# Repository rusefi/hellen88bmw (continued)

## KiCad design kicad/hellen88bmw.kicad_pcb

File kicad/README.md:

Part of https://github.com/andreika-git/hellen-one family

https://docs.google.com/spreadsheets/d/1OiEaak7TElKwF-fXWvl9Dk-fD84a0NENe6lOwhXiOe4/

Inspired by https://github.com/rusefi/hw_88_bmw

https://github.com/rusefi/hw_microRusEfi

We shall start from https://github.com/rusefi/hellen121vag but using https://github.com/rusefi/hw_88_bmw shape and pinout.

Plan:

1) merge https://github.com/rusefi/hellen121vag MCU stuff with shape of https://github.com/rusefi/hw_88_bmw

from https://github.com/rusefi/hw_88_bmw we keep
   1) outline
   2) ignition coil drivers (we actually add two more - hw_88_bmw was a 6 cylinder board, we make a 8 cylinder ECU)
   3) MAP sensor position
   4) keep SD card somewhere
   5) 88 jumpers

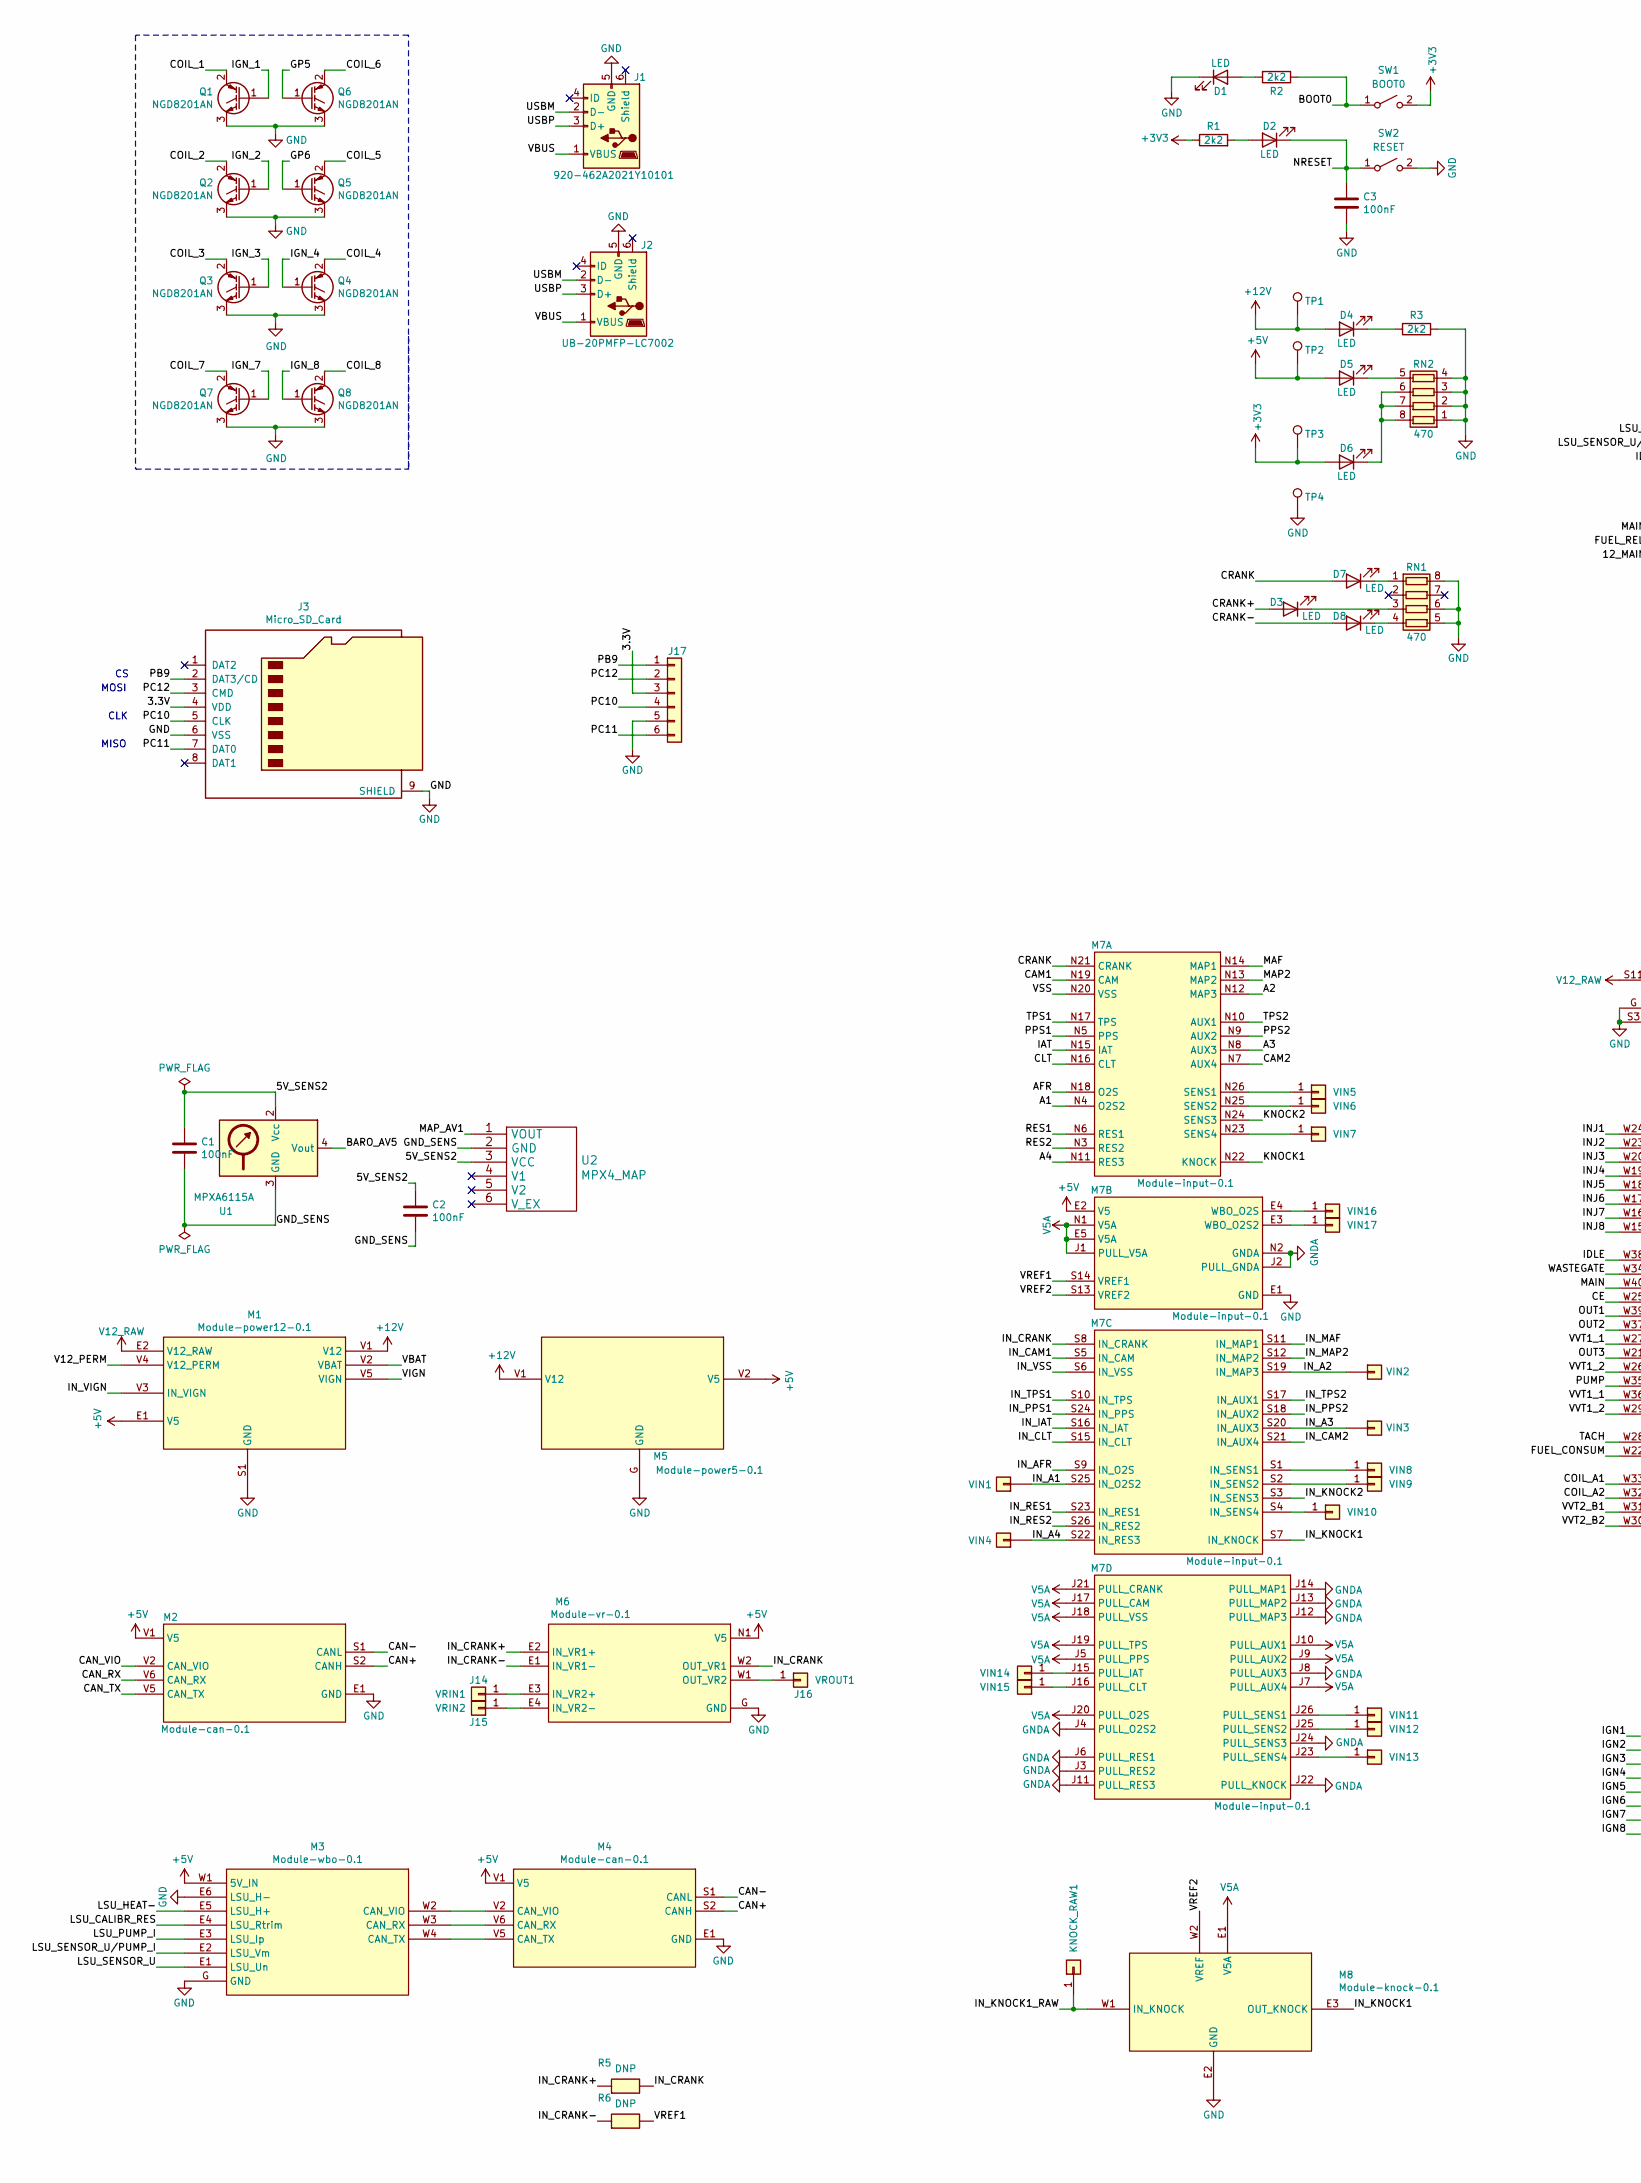
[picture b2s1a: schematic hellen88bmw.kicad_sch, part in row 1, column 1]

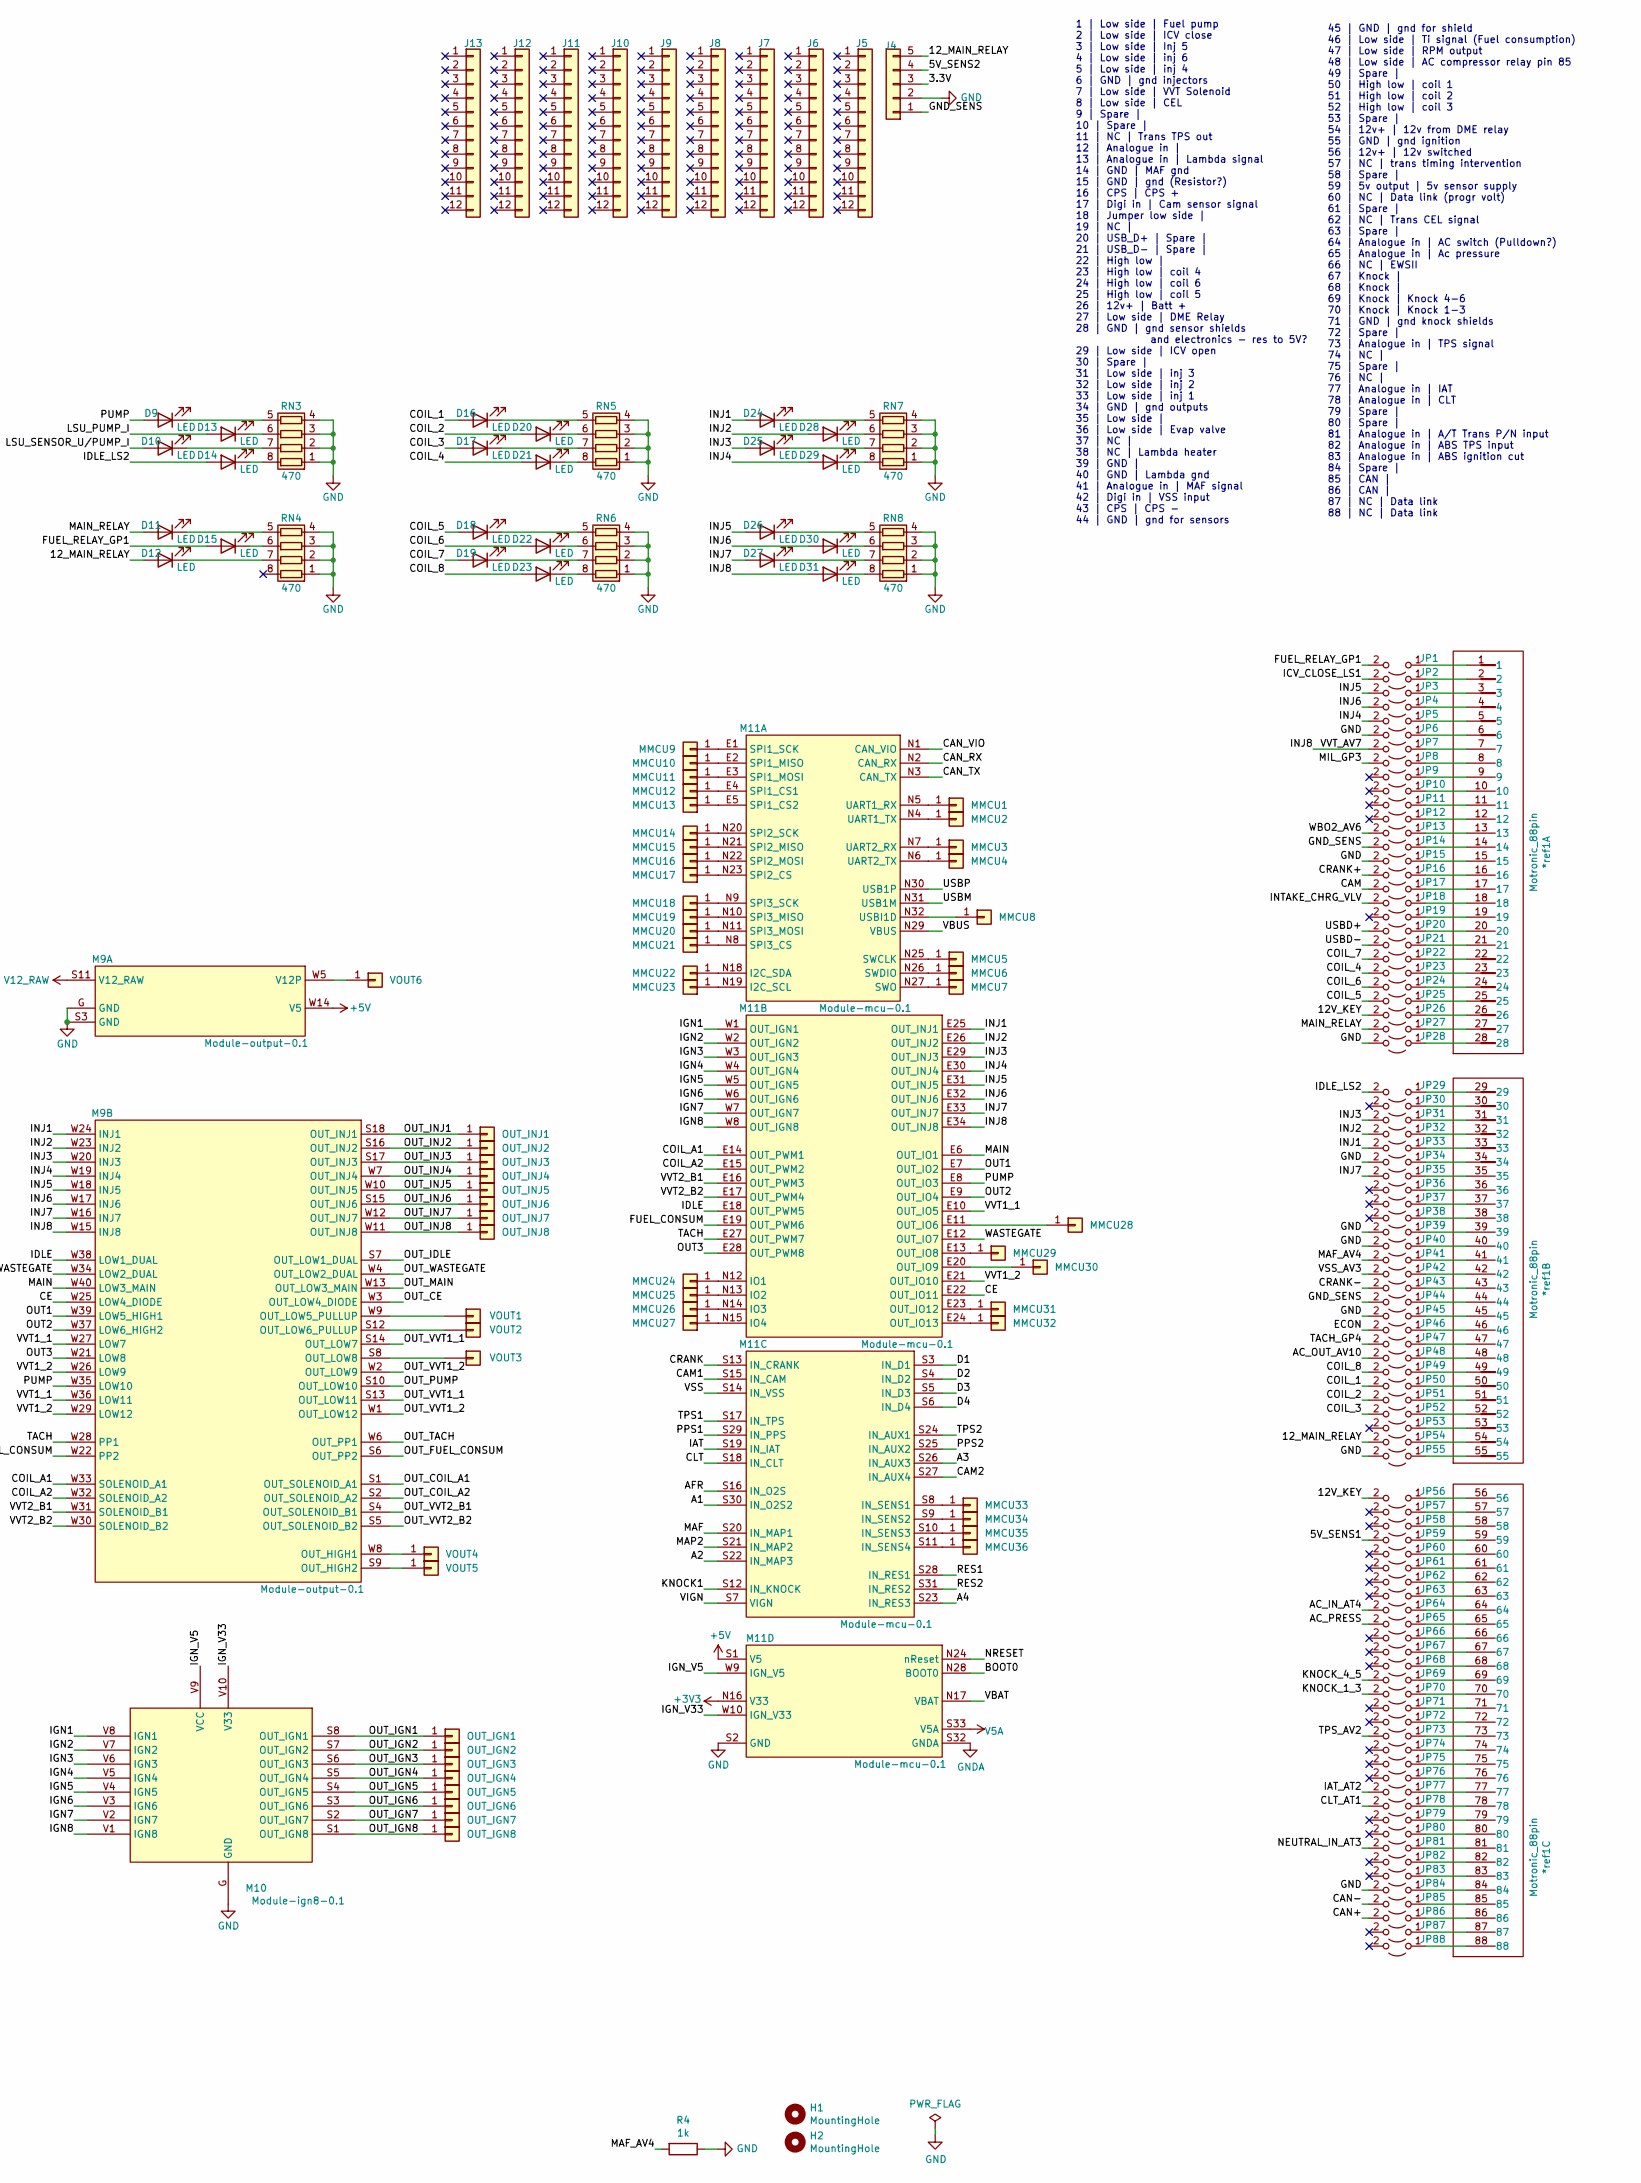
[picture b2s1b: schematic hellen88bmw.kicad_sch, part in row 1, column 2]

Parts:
*ref1: Motronic_88pin; 88pin_STS
C1, C2, C3: 100nF; C_0603_1608Metric; LCSC C49678
D1, D2, D3, D4, D5, D6, D7, D8, D9, D10, D11, D12, D13, D14, D15, D16, D17, D18, D19, D20, D21, D22, D23, D24, D25, D26, D27, D28, D29, D30, D31: LED; LED_0603_1608Metric
H1, H2: MountingHole; MountingHole_4.3mm_M4_DIN965
J1: 920-462A2021Y10101; USB-MINI-B-VERTICAL; LCSC C13453
J2: UB-20PMFP-LC7002; PinHeader_1x05_P2.00mm_Vertical; LCSC C13453
J3: Micro_SD_Card; 693072010801
J4: Conn_01x05; PinHeader_1x05_P2.54mm_Vertical
J5, J6, J7, J8, J9, J10, J11, J12, J13: Conn_01x12; PinHeader_1x12_P2.54mm_Vertical
J14: VRIN1; PinHeader_1x01_P1.00mm_Vertical
J15: VRIN2; PinHeader_1x01_P1.00mm_Vertical
J16: VROUT1; PinHeader_1x01_P1.00mm_Vertical
J17: SD; PinHeader_1x06_P2.54mm_Vertical
JP1: Jumper_2_Open; SM0805_jumper; LCSC C17477
JP2, JP3, JP4, JP5, JP6, JP7, JP8, JP9, JP10, JP11, JP12, JP13, JP14, JP15, JP16, JP17, JP18, JP19, JP20, JP21, JP22, JP23, JP24, JP25, JP26, JP27, JP28, JP29, JP30, JP31, JP32, JP33, JP34, JP35, JP36, JP37, JP38, JP39, JP40, JP41, JP42, JP43, JP44, JP45, JP46, JP47, JP48, JP49, JP50, JP51, JP52, JP53, JP54, JP55, JP56, JP57, JP58, JP59, JP60, JP61, JP62, JP63, JP64, JP65, JP66, JP67, JP68, JP69, JP70, JP71, JP72, JP73, JP74, JP75, JP76, JP77, JP78, JP79, JP80, JP81, JP82, JP83, JP84, JP85, JP86, JP87, JP88: Jumper_2_Open; SM0805_jumper
KNOCK_RAW1: IN_KNOCK1_RAW; PinHeader_1x01_P1.00mm_Vertical
M1: Module-power12-0.1; MOD_HELLEN_POWER_12
M2, M4: Module-can-0.1; MOD_HELLEN_CAN
M3: Module-wbo-0.1; MOD_HELLEN_WBO
M5: Module-power5-0.1; MOD_HELLEN_POWER_5
M6: Module-vr-0.1; MOD_HELLEN_VR
M7: Module-input-0.1; MOD_HELLEN_INPUT
M8: Module-knock-0.1; MOD_HELLEN_KNOCK
M9: Module-output-0.1; MOD_HELLEN_OUTPUT
M10: Module-ign8-0.1; MOD_HELLEN_IGN8
M11: Module-mcu-0.1; MOD_HELLEN_MCU
MMCU1: MMCU1; PinHeader_1x01_P1.00mm_Vertical
MMCU2, MMCU3, MMCU4, MMCU5, MMCU6, MMCU7, MMCU8, MMCU9, MMCU10, MMCU11, MMCU12, MMCU13, MMCU14, MMCU15, MMCU16, MMCU17, MMCU18, MMCU19, MMCU20, MMCU21, MMCU22, MMCU23, MMCU24, MMCU25, MMCU26, MMCU27, MMCU28, MMCU29, MMCU30, MMCU31, MMCU32, MMCU33, MMCU34, MMCU35, MMCU36: MMCU; PinHeader_1x01_P1.00mm_Vertical
OUT_IGN1: OUT_IGN1; PinHeader_1x01_P1.00mm_Vertical
OUT_IGN2: OUT_IGN2; PinHeader_1x01_P1.00mm_Vertical
OUT_IGN3: OUT_IGN3; PinHeader_1x01_P1.00mm_Vertical
OUT_IGN4: OUT_IGN4; PinHeader_1x01_P1.00mm_Vertical
OUT_IGN5: OUT_IGN5; PinHeader_1x01_P1.00mm_Vertical
OUT_IGN6: OUT_IGN6; PinHeader_1x01_P1.00mm_Vertical
OUT_IGN7: OUT_IGN7; PinHeader_1x01_P1.00mm_Vertical
OUT_IGN8: OUT_IGN8; PinHeader_1x01_P1.00mm_Vertical
OUT_INJ1: OUT_INJ1; PinHeader_1x01_P1.00mm_Vertical
OUT_INJ2: OUT_INJ2; PinHeader_1x01_P1.00mm_Vertical
OUT_INJ3: OUT_INJ3; PinHeader_1x01_P1.00mm_Vertical
OUT_INJ4: OUT_INJ4; PinHeader_1x01_P1.00mm_Vertical
OUT_INJ5: OUT_INJ5; PinHeader_1x01_P1.00mm_Vertical
OUT_INJ6: OUT_INJ6; PinHeader_1x01_P1.00mm_Vertical
OUT_INJ7: OUT_INJ7; PinHeader_1x01_P1.00mm_Vertical
OUT_INJ8: OUT_INJ8; PinHeader_1x01_P1.00mm_Vertical
Q1, Q2, Q3, Q4, Q5, Q7, Q8: NGD8201AN; TO-252-2
Q6: NGD8201AN; TO-252-2; LCSC C151649
R1, R2, R3: 2k2; R_0603_1608Metric
R4: 1k; R_0603_1608Metric; LCSC C17513
R5, R6: DNP; R_0603_1608Metric
RN1, RN2, RN3, RN4, RN5, RN6, RN7, RN8: 470; R_Array_Concave_4x0603
SW1: BOOT0; SW_SPST_B3U-1000P-B
SW2: RESET; SW_SPST_B3U-1000P-B
TP1, TP2, TP3, TP4: TestPoint; TestPoint_Pad_D1.0mm
U1: MPXA6115A; SSO-8_6.8x5.9mm_P1.27mm_Clearance7mm
U2: MPX4_MAP; MPX-4_MAP
VIN1, VIN2, VIN3, VIN4: Pad; PinHeader_1x01_P1.00mm_Vertical
VIN5: VIN5; PinHeader_1x01_P1.00mm_Vertical
VIN6: VIN6; PinHeader_1x01_P1.00mm_Vertical
VIN7: VIN7; PinHeader_1x01_P1.00mm_Vertical
VIN8: VIN8; PinHeader_1x01_P1.00mm_Vertical
VIN9: VIN9; PinHeader_1x01_P1.00mm_Vertical
VIN10: VIN10; PinHeader_1x01_P1.00mm_Vertical
VIN11: VIN11; PinHeader_1x01_P1.00mm_Vertical
VIN12: VIN12; PinHeader_1x01_P1.00mm_Vertical
VIN13: VIN13; PinHeader_1x01_P1.00mm_Vertical
VIN14: VIN14; PinHeader_1x01_P1.00mm_Vertical
VIN15: VIN15; PinHeader_1x01_P1.00mm_Vertical
VIN16: VIN16; PinHeader_1x01_P1.00mm_Vertical
VIN17: VIN17; PinHeader_1x01_P1.00mm_Vertical
VOUT1, VOUT2, VOUT3: Pad; PinHeader_1x01_P1.00mm_Vertical
VOUT4: VOUT4; PinHeader_1x01_P1.00mm_Vertical
VOUT5: VOUT5; PinHeader_1x01_P1.00mm_Vertical
VOUT6: VOUT6; PinHeader_1x01_P1.00mm_Vertical

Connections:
+3V3: D6.2 (A), M11.N16 (V33), R1.1, SW1.2 (B), TP3.1
+5V: D5.2 (A), M1.E1 (V5), M2.V1 (V5), M3.W1 (5V_IN), M4.V1 (V5), M5.V2 (V5), M6.N1 (V5), M7.E2 (V5), M9.W14 (V5), M11.S1 (V5), TP2.1
+12V: D4.2 (A), M1.V1 (V12), M5.V1 (V12), TP1.1
/3.3V: J3.4 (VDD), J4.3, J17.3
/5V_SENS1: JP59.2 (B)
/5V_SENS2: C1.1, C2.1, J4.4, U1.2 (Vcc), U2.3 (VCC)
/12V_KEY: JP26.2 (B), JP56.2 (B)
/12_MAIN_RELAY: D12.2 (A), J4.5, JP54.2 (B)
/A1: M7.N4 (O2S2), M11.S30 (IN_O2S2)
/A2: M7.N12 (MAP3), M11.S22 (IN_MAP3)
/A3: M7.N8 (AUX3), M11.S26 (IN_AUX3)
/A4: M7.N11 (RES3), M11.S23 (IN_RES3)
/AC_IN_AT4: JP64.2 (B)
/AC_OUT_AV10: JP48.2 (B)
/AC_PRESS: JP65.2 (B)
/AFR: M7.N18 (O2S), M11.S16 (IN_O2S)
/BARO_AV5: U1.4 (Vout)
/BOOT0: M11.N28 (BOOT0), R2.1, SW1.1 (A)
/CAM: JP17.2 (B)
/CAM1: M7.N19 (CAM), M11.S15 (IN_CAM)
/CAM2: M7.N7 (AUX4), M11.S27 (IN_AUX4)
/CAN+: JP86.2 (B), M2.S2 (CANH), M4.S2 (CANH)
/CAN-: JP85.2 (B), M2.S1 (CANL), M4.S1 (CANL)
/CAN_RX: M2.V6 (CAN_RX), M11.N2 (CAN_RX)
/CAN_TX: M2.V5 (CAN_TX), M11.N3 (CAN_TX)
/CAN_VIO: M2.V2 (CAN_VIO), M11.N1 (CAN_VIO)
/CE: M9.W25 (LOW4_DIODE), M11.E22 (OUT_IO11)
/CLT: M7.N16 (CLT), M11.S18 (IN_CLT)
/CLT_AT1: JP78.2 (B)
/COIL_1: D16.2 (A), JP50.2 (B), Q1.2 (C)
/COIL_2: D20.2 (A), JP51.2 (B), Q2.2 (C)
/COIL_3: D17.2 (A), JP52.2 (B), Q3.2 (C)
/COIL_4: D21.2 (A), JP23.2 (B), Q4.2 (C)
/COIL_5: D18.2 (A), JP25.2 (B), Q5.2 (C)
/COIL_6: D22.2 (A), JP24.2 (B), Q6.2 (C)
/COIL_7: D19.2 (A), JP22.2 (B), Q7.2 (C)
/COIL_8: D23.2 (A), JP49.2 (B), Q8.2 (C)
/COIL_A1: M9.W33 (SOLENOID_A1), M11.E14 (OUT_PWM1)
/COIL_A2: M9.W32 (SOLENOID_A2), M11.E15 (OUT_PWM2)
/CRANK: D7.2 (A), M7.N21 (CRANK), M11.S13 (IN_CRANK)
/CRANK+: D3.2 (A), JP16.2 (B)
/CRANK-: D8.2 (A), JP43.2 (B)
/D1: M11.S3 (IN_D1)
/D2: M11.S4 (IN_D2)
/D3: M11.S5 (IN_D3)
/D4: M11.S6 (IN_D4)
/ECON: JP46.2 (B)
/FUEL_CONSUM: M9.W22 (PP2), M11.E19 (OUT_PWM6)
/FUEL_RELAY_GP1: D15.2 (A), JP1.2 (B)
/GND_SENS: C1.2, C2.2, J4.1, JP14.2 (B), JP44.2 (B), U1.3 (GND), U2.2 (GND)
/GP5: Q6.1 (G)
/GP6: Q5.1 (G)
/IAT: M7.N15 (IAT), M11.S19 (IN_IAT)
/IAT_AT2: JP77.2 (B)
/ICV_CLOSE_LS1: JP2.2 (B)
/IDLE: M9.W38 (LOW1_DUAL), M11.E18 (OUT_PWM5)
/IDLE_LS2: D14.2 (A), JP29.2 (B)
/IGN1: M10.V8 (IGN1), M11.W1 (OUT_IGN1)
/IGN2: M10.V7 (IGN2), M11.W2 (OUT_IGN2)
/IGN3: M10.V6 (IGN3), M11.W3 (OUT_IGN3)
/IGN4: M10.V5 (IGN4), M11.W4 (OUT_IGN4)
/IGN5: M10.V4 (IGN5), M11.W5 (OUT_IGN5)
/IGN6: M10.V3 (IGN6), M11.W6 (OUT_IGN6)
/IGN7: M10.V2 (IGN7), M11.W7 (OUT_IGN7)
/IGN8: M10.V1 (IGN8), M11.W8 (OUT_IGN8)
/IGN_1: Q1.1 (G)
/IGN_2: Q2.1 (G)
/IGN_3: Q3.1 (G)
/IGN_4: Q4.1 (G)
/IGN_7: Q7.1 (G)
/IGN_8: Q8.1 (G)
/IGN_V5: M10.V9 (VCC), M11.W9 (IGN_V5)
/IGN_V33: M10.V10 (V33), M11.W10 (IGN_V33)
/INJ1: D24.2 (A), JP33.2 (B), M9.W24 (INJ1), M11.E25 (OUT_INJ1)
/INJ2: D28.2 (A), JP32.2 (B), M9.W23 (INJ2), M11.E26 (OUT_INJ2)
/INJ3: D25.2 (A), JP31.2 (B), M9.W20 (INJ3), M11.E29 (OUT_INJ3)
/INJ4: D29.2 (A), JP5.2 (B), M9.W19 (INJ4), M11.E30 (OUT_INJ4)
/INJ5: D26.2 (A), JP3.2 (B), M9.W18 (INJ5), M11.E31 (OUT_INJ5)
/INJ6: D30.2 (A), JP4.2 (B), M9.W17 (INJ6), M11.E32 (OUT_INJ6)
/INJ7: D27.2 (A), JP35.2 (B), M9.W16 (INJ7), M11.E33 (OUT_INJ7)
/INJ8: D31.2 (A), JP7.2 (B), M9.W15 (INJ8), M11.E34 (OUT_INJ8)
/INTAKE_CHRG_VLV: JP18.2 (B)
/IN_A1: M7.S25 (IN_O2S2), VIN1.1
/IN_A2: M7.S19 (IN_MAP3), VIN2.1
/IN_A3: M7.S20 (IN_AUX3), VIN3.1
/IN_A4: M7.S22 (IN_RES3), VIN4.1
/IN_AFR: M7.S9 (IN_O2S)
/IN_CAM1: M7.S5 (IN_CAM)
/IN_CAM2: M7.S21 (IN_AUX4)
/IN_CLT: M7.S15 (IN_CLT)
/IN_CRANK: M6.W2 (OUT_VR1), M7.S8 (IN_CRANK), R5.2
/IN_CRANK+: M6.E2 (IN_VR1+), R5.1
/IN_CRANK-: M6.E1 (IN_VR1-), R6.1
/IN_IAT: M7.S16 (IN_IAT)
/IN_KNOCK1: M7.S7 (IN_KNOCK), M8.E3 (OUT_KNOCK)
/IN_KNOCK1_RAW: KNOCK_RAW1.1, M8.W1 (IN_KNOCK)
/IN_KNOCK2: M7.S3 (IN_SENS3)
/IN_MAF: M7.S11 (IN_MAP1)
/IN_MAP2: M7.S12 (IN_MAP2)
/IN_PPS1: M7.S24 (IN_PPS)
/IN_PPS2: M7.S18 (IN_AUX2)
/IN_RES1: M7.S23 (IN_RES1)
/IN_RES2: M7.S26 (IN_RES2)
/IN_TPS1: M7.S10 (IN_TPS)
/IN_TPS2: M7.S17 (IN_AUX1)
/IN_VIGN: M1.V3 (IN_VIGN)
/IN_VSS: M7.S6 (IN_VSS)
/KNOCK1: M7.N22 (KNOCK), M11.S12 (IN_KNOCK)
/KNOCK2: M7.N24 (SENS3)
/KNOCK_1_3: JP70.2 (B)
/KNOCK_4_5: JP69.2 (B)
/LSU_CALIBR_RES: M3.E4 (LSU_Rtrim)
/LSU_HEAT-: M3.E5 (LSU_H+)
/LSU_PUMP_I: D13.2 (A), M3.E3 (LSU_Ip)
/LSU_SENSOR_U: M3.E1 (LSU_Un)
/LSU_SENSOR_U/PUMP_I: D10.2 (A), M3.E2 (LSU_Vm)
/MAF: M7.N14 (MAP1), M11.S20 (IN_MAP1)
/MAF_AV4: JP41.2 (B), R4.2
/MAIN: M9.W40 (LOW3_MAIN), M11.E6 (OUT_IO1)
/MAIN_RELAY: D11.2 (A), JP27.2 (B)
/MAP2: M7.N13 (MAP2), M11.S21 (IN_MAP2)
/MAP_AV1: U2.1 (VOUT)
/MIL_GP3: JP8.2 (B)
/NEUTRAL_IN_AT3: JP81.2 (B)
/NRESET: C3.1, D2.1 (K), M11.N24 (nReset), SW2.1 (A)
/OUT1: M9.W39 (LOW5_HIGH1), M11.E7 (OUT_IO2)
/OUT2: M9.W37 (LOW6_HIGH2), M11.E9 (OUT_IO4)
/OUT3: M9.W21 (LOW8), M11.E28 (OUT_PWM8)
/OUT_CE: M9.W3 (OUT_LOW4_DIODE)
/OUT_COIL_A1: M9.S1 (OUT_SOLENOID_A1)
/OUT_COIL_A2: M9.S2 (OUT_SOLENOID_A2)
/OUT_FUEL_CONSUM: M9.S6 (OUT_PP2)
/OUT_IDLE: M9.S7 (OUT_LOW1_DUAL)
/OUT_IGN1: M10.S8 (OUT_IGN1), OUT_IGN1.1
/OUT_IGN2: M10.S7 (OUT_IGN2), OUT_IGN2.1
/OUT_IGN3: M10.S6 (OUT_IGN3), OUT_IGN3.1
/OUT_IGN4: M10.S5 (OUT_IGN4), OUT_IGN4.1
/OUT_IGN5: M10.S4 (OUT_IGN5), OUT_IGN5.1
/OUT_IGN6: M10.S3 (OUT_IGN6), OUT_IGN6.1
/OUT_IGN7: M10.S2 (OUT_IGN7), OUT_IGN7.1
/OUT_IGN8: M10.S1 (OUT_IGN8), OUT_IGN8.1
/OUT_INJ1: M9.S18 (OUT_INJ1), OUT_INJ1.1
/OUT_INJ2: M9.S16 (OUT_INJ2), OUT_INJ2.1
/OUT_INJ3: M9.S17 (OUT_INJ3), OUT_INJ3.1
/OUT_INJ4: M9.W7 (OUT_INJ4), OUT_INJ4.1
/OUT_INJ5: M9.W10 (OUT_INJ5), OUT_INJ5.1
/OUT_INJ6: M9.S15 (OUT_INJ6), OUT_INJ6.1
/OUT_INJ7: M9.W12 (OUT_INJ7), OUT_INJ7.1
/OUT_INJ8: M9.W11 (OUT_INJ8), OUT_INJ8.1
/OUT_MAIN: M9.W13 (OUT_LOW3_MAIN)
/OUT_PUMP: M9.S10 (OUT_LOW10)
/OUT_TACH: M9.W6 (OUT_PP1)
/OUT_VVT1_1: M9.S13 (OUT_LOW11), M9.S14 (OUT_LOW7)
/OUT_VVT1_2: M9.W1 (OUT_LOW12), M9.W2 (OUT_LOW9)
/OUT_VVT2_B1: M9.S4 (OUT_SOLENOID_B1)
/OUT_VVT2_B2: M9.S5 (OUT_SOLENOID_B2)
/OUT_WASTEGATE: M9.W4 (OUT_LOW2_DUAL)
/PB9: J3.2 (DAT3/CD), J17.1
/PC10: J3.5 (CLK), J17.4
/PC11: J3.7 (DAT0), J17.6
/PC12: J3.3 (CMD), J17.2
/PPS1: M7.N5 (PPS), M11.S29 (IN_PPS)
/PPS2: M7.N9 (AUX2), M11.S25 (IN_AUX2)
/PUMP: D9.2 (A), M9.W35 (LOW10), M11.E8 (OUT_IO3)
/RES1: M7.N6 (RES1), M11.S28 (IN_RES1)
/RES2: M7.N3 (RES2), M11.S31 (IN_RES2)
/TACH: M9.W28 (PP1), M11.E27 (OUT_PWM7)
/TACH_GP4: JP47.2 (B)
/TPS1: M7.N17 (TPS), M11.S17 (IN_TPS)
/TPS2: M7.N10 (AUX1), M11.S24 (IN_AUX1)
/TPS_AV2: JP73.2 (B)
/USBD+: JP20.2 (B)
/USBD-: JP21.2 (B)
/USBM: J1.2 (D-), J2.2 (D-), M11.N31 (USB1M)
/USBP: J1.3 (D+), J2.3 (D+), M11.N30 (USB1P)
/V12_PERM: M1.V4 (V12_PERM)
/VBAT: M1.V2 (VBAT), M11.N17 (VBAT)
/VBUS: J1.1 (VBUS), J2.1 (VBUS), M11.N29 (VBUS)
/VIGN: M1.V5 (VIGN), M11.S7 (VIGN)
/VREF1: M7.S14 (VREF1), R6.2
/VREF2: M7.S13 (VREF2), M8.W2 (VREF)
/VSS: M7.N20 (VSS), M11.S14 (IN_VSS)
/VSS_AV3: JP42.2 (B)
/VVT1_1: M9.W27 (LOW7), M9.W36 (LOW11), M11.E10 (OUT_IO5)
/VVT1_2: M9.W26 (LOW9), M9.W29 (LOW12), M11.E21 (OUT_IO10)
/VVT2_B1: M9.W31 (SOLENOID_B1), M11.E16 (OUT_PWM3)
/VVT2_B2: M9.W30 (SOLENOID_B2), M11.E17 (OUT_PWM4)
/WASTEGATE: M9.W34 (LOW2_DUAL), M11.E12 (OUT_IO7)
/WBO2_AV6: JP13.2 (B)
GND: C3.2, D1.1 (K), J1.5 (GND), J2.5 (GND), J3.6 (VSS), J3.9 (SHIELD), J4.2, J17.5, JP6.2 (B), JP15.2 (B), JP28.2 (B), JP34.2 (B), JP39.2 (B), JP40.2 (B), JP45.2 (B), JP55.2 (B), JP84.2 (B), M1.S1 (GND), M2.E1 (GND), M3.E6 (LSU_H-), M3.G (GND), M4.E1 (GND), M5.G (GND), M6.G (GND), M7.E1 (GND), M8.E2 (GND), M9.G (GND), M9.S3 (GND), M10.G (GND), M11.S2 (GND), Q1.3 (E), Q2.3 (E), Q3.3 (E), Q4.3 (E), Q5.3 (E), Q6.3 (E), Q7.3 (E), Q8.3 (E), R3.2, R4.1, RN1.5 (R4.2), RN1.6 (R3.2), RN1.8 (R1.2), RN2.1 (R1.1), RN2.2 (R2.1), RN2.3 (R3.1), RN2.4 (R4.1), RN3.1 (R1.1), RN3.2 (R2.1), RN3.3 (R3.1), RN3.4 (R4.1), RN4.1 (R1.1), RN4.2 (R2.1), RN4.3 (R3.1), RN4.4 (R4.1), RN5.1 (R1.1), RN5.2 (R2.1), RN5.3 (R3.1), RN5.4 (R4.1), RN6.1 (R1.1), RN6.2 (R2.1), RN6.3 (R3.1), RN6.4 (R4.1), RN7.1 (R1.1), RN7.2 (R2.1), RN7.3 (R3.1), RN7.4 (R4.1), RN8.1 (R1.1), RN8.2 (R2.1), RN8.3 (R3.1), RN8.4 (R4.1), SW2.2 (B), TP4.1
GNDA: M7.J2 (PULL_GNDA), M7.J3 (PULL_RES2), M7.J4 (PULL_O2S2), M7.J6 (PULL_RES1), M7.J8 (PULL_AUX3), M7.J11 (PULL_RES3), M7.J12 (PULL_MAP3), M7.J13 (PULL_MAP2), M7.J14 (PULL_MAP1), M7.J22 (PULL_KNOCK), M7.J24 (PULL_SENS3), M7.N2 (GNDA), M11.S32 (GNDA)
unnamed: *ref1.1, JP1.1 (A)
unnamed: *ref1.2, JP2.1 (A)
unnamed: *ref1.3, JP3.1 (A)
unnamed: *ref1.4, JP4.1 (A)
unnamed: *ref1.5, JP5.1 (A)
unnamed: *ref1.6, JP6.1 (A)
unnamed: *ref1.7, JP7.1 (A)
unnamed: *ref1.8, JP8.1 (A)
unnamed: *ref1.9, JP9.1 (A)
unnamed: *ref1.10, JP10.1 (A)
unnamed: *ref1.11, JP11.1 (A)
unnamed: *ref1.12, JP12.1 (A)
unnamed: *ref1.13, JP13.1 (A)
unnamed: *ref1.14, JP14.1 (A)
unnamed: *ref1.15, JP15.1 (A)
unnamed: *ref1.16, JP16.1 (A)
unnamed: *ref1.17, JP17.1 (A)
unnamed: *ref1.18, JP18.1 (A)
unnamed: *ref1.19, JP19.1 (A)
unnamed: *ref1.20, JP20.1 (A)
unnamed: *ref1.21, JP21.1 (A)
unnamed: *ref1.22, JP22.1 (A)
unnamed: *ref1.23, JP23.1 (A)
unnamed: *ref1.24, JP24.1 (A)
unnamed: *ref1.25, JP25.1 (A)
unnamed: *ref1.26, JP26.1 (A)
unnamed: *ref1.27, JP27.1 (A)
unnamed: *ref1.28, JP28.1 (A)
unnamed: *ref1.29, JP29.1 (A)
unnamed: *ref1.30, JP30.1 (A)
unnamed: *ref1.31, JP31.1 (A)
unnamed: *ref1.32, JP32.1 (A)
unnamed: *ref1.33, JP33.1 (A)
unnamed: *ref1.34, JP34.1 (A)
unnamed: *ref1.35, JP35.1 (A)
unnamed: *ref1.36, JP36.1 (A)
unnamed: *ref1.37, JP37.1 (A)
unnamed: *ref1.38, JP38.1 (A)
unnamed: *ref1.39, JP39.1 (A)
unnamed: *ref1.40, JP40.1 (A)
unnamed: *ref1.41, JP41.1 (A)
unnamed: *ref1.42, JP42.1 (A)
unnamed: *ref1.43, JP43.1 (A)
unnamed: *ref1.44, JP44.1 (A)
unnamed: *ref1.45, JP45.1 (A)
unnamed: *ref1.46, JP46.1 (A)
unnamed: *ref1.47, JP47.1 (A)
unnamed: *ref1.48, JP48.1 (A)
unnamed: *ref1.49, JP49.1 (A)
unnamed: *ref1.50, JP50.1 (A)
unnamed: *ref1.51, JP51.1 (A)
unnamed: *ref1.52, JP52.1 (A)
unnamed: *ref1.53, JP53.1 (A)
unnamed: *ref1.54, JP54.1 (A)
unnamed: *ref1.55, JP55.1 (A)
unnamed: *ref1.56, JP56.1 (A)
unnamed: *ref1.57, JP57.1 (A)
unnamed: *ref1.58, JP58.1 (A)
unnamed: *ref1.59, JP59.1 (A)
unnamed: *ref1.60, JP60.1 (A)
unnamed: *ref1.61, JP61.1 (A)
unnamed: *ref1.62, JP62.1 (A)
unnamed: *ref1.63, JP63.1 (A)
unnamed: *ref1.64, JP64.1 (A)
unnamed: *ref1.65, JP65.1 (A)
unnamed: *ref1.66, JP66.1 (A)
unnamed: *ref1.67, JP67.1 (A)
unnamed: *ref1.68, JP68.1 (A)
unnamed: *ref1.69, JP69.1 (A)
unnamed: *ref1.70, JP70.1 (A)
unnamed: *ref1.71, JP71.1 (A)
unnamed: *ref1.72, JP72.1 (A)
unnamed: *ref1.73, JP73.1 (A)
unnamed: *ref1.74, JP74.1 (A)
unnamed: *ref1.75, JP75.1 (A)
unnamed: *ref1.76, JP76.1 (A)
unnamed: *ref1.77, JP77.1 (A)
unnamed: *ref1.78, JP78.1 (A)
unnamed: *ref1.79, JP79.1 (A)
unnamed: *ref1.80, JP80.1 (A)
unnamed: *ref1.81, JP81.1 (A)
unnamed: *ref1.82, JP82.1 (A)
unnamed: *ref1.83, JP83.1 (A)
unnamed: *ref1.84, JP84.1 (A)
unnamed: *ref1.85, JP85.1 (A)
unnamed: *ref1.86, JP86.1 (A)
unnamed: *ref1.87, JP87.1 (A)
unnamed: *ref1.88, JP88.1 (A)
unnamed: D1.2 (A), R2.2
unnamed: D2.2 (A), R1.2
unnamed: D3.1 (K), RN1.3 (R3.1)
unnamed: D4.1 (K), R3.1
unnamed: D5.1 (K), RN2.5 (R4.2)
unnamed: D6.1 (K), RN2.6 (R3.2), RN2.7 (R2.2), RN2.8 (R1.2)
unnamed: D7.1 (K), RN1.1 (R1.1)
unnamed: D8.1 (K), RN1.4 (R4.1)
unnamed: D9.1 (K), RN3.5 (R4.2)
unnamed: D10.1 (K), RN3.7 (R2.2)
unnamed: D11.1 (K), RN4.5 (R4.2)
unnamed: D12.1 (K), RN4.7 (R2.2)
unnamed: D13.1 (K), RN3.6 (R3.2)
unnamed: D14.1 (K), RN3.8 (R1.2)
unnamed: D15.1 (K), RN4.6 (R3.2)
unnamed: D16.1 (K), RN5.5 (R4.2)
unnamed: D17.1 (K), RN5.7 (R2.2)
unnamed: D18.1 (K), RN6.5 (R4.2)
unnamed: D19.1 (K), RN6.7 (R2.2)
unnamed: D20.1 (K), RN5.6 (R3.2)
unnamed: D21.1 (K), RN5.8 (R1.2)
unnamed: D22.1 (K), RN6.6 (R3.2)
unnamed: D23.1 (K), RN6.8 (R1.2)
unnamed: D24.1 (K), RN7.5 (R4.2)
unnamed: D25.1 (K), RN7.7 (R2.2)
unnamed: D26.1 (K), RN8.5 (R4.2)
unnamed: D27.1 (K), RN8.7 (R2.2)
unnamed: D28.1 (K), RN7.6 (R3.2)
unnamed: D29.1 (K), RN7.8 (R1.2)
unnamed: D30.1 (K), RN8.6 (R3.2)
unnamed: D31.1 (K), RN8.8 (R1.2)
unnamed: J14.1, M6.E3 (IN_VR2+)
unnamed: J15.1, M6.E4 (IN_VR2-)
unnamed: J16.1, M6.W1 (OUT_VR2)
unnamed: M3.W2 (CAN_VIO), M4.V2 (CAN_VIO)
unnamed: M3.W3 (CAN_RX), M4.V6 (CAN_RX)
unnamed: M3.W4 (CAN_TX), M4.V5 (CAN_TX)
unnamed: M7.E3 (WBO_O2S2), VIN17.1
unnamed: M7.E4 (WBO_O2S), VIN16.1
unnamed: M7.J15 (PULL_IAT), VIN14.1
unnamed: M7.J16 (PULL_CLT), VIN15.1
unnamed: M7.J23 (PULL_SENS4), VIN13.1
unnamed: M7.J25 (PULL_SENS2), VIN12.1
unnamed: M7.J26 (PULL_SENS1), VIN11.1
unnamed: M7.N23 (SENS4), VIN7.1
unnamed: M7.N25 (SENS2), VIN6.1
unnamed: M7.N26 (SENS1), VIN5.1
unnamed: M7.S1 (IN_SENS1), VIN8.1
unnamed: M7.S2 (IN_SENS2), VIN9.1
unnamed: M7.S4 (IN_SENS4), VIN10.1
unnamed: M9.S8 (OUT_LOW8), VOUT3.1
unnamed: M9.S9 (OUT_HIGH2), VOUT5.1
unnamed: M9.S12 (OUT_LOW6_PULLUP), VOUT2.1
unnamed: M9.W5 (V12P), VOUT6.1
unnamed: M9.W8 (OUT_HIGH1), VOUT4.1
unnamed: M9.W9 (OUT_LOW5_PULLUP), VOUT1.1
unnamed: M11.E1 (SPI1_SCK), MMCU9.1
unnamed: M11.E2 (SPI1_MISO), MMCU10.1
unnamed: M11.E3 (SPI1_MOSI), MMCU11.1
unnamed: M11.E4 (SPI1_CS1), MMCU12.1
unnamed: M11.E5 (SPI1_CS2), MMCU13.1
unnamed: M11.E11 (OUT_IO6), MMCU28.1
unnamed: M11.E13 (OUT_IO8), MMCU29.1
unnamed: M11.E20 (OUT_IO9), MMCU30.1
unnamed: M11.E23 (OUT_IO12), MMCU31.1
unnamed: M11.E24 (OUT_IO13), MMCU32.1
unnamed: M11.N4 (UART1_TX), MMCU2.1
unnamed: M11.N5 (UART1_RX), MMCU1.1
unnamed: M11.N6 (UART2_TX), MMCU4.1
unnamed: M11.N7 (UART2_RX), MMCU3.1
unnamed: M11.N8 (SPI3_CS), MMCU21.1
unnamed: M11.N9 (SPI3_SCK), MMCU18.1
unnamed: M11.N10 (SPI3_MISO), MMCU19.1
unnamed: M11.N11 (SPI3_MOSI), MMCU20.1
unnamed: M11.N12 (IO1), MMCU24.1
unnamed: M11.N13 (IO2), MMCU25.1
unnamed: M11.N14 (IO3), MMCU26.1
unnamed: M11.N15 (IO4), MMCU27.1
unnamed: M11.N18 (I2C_SDA), MMCU22.1
unnamed: M11.N19 (I2C_SCL), MMCU23.1
unnamed: M11.N20 (SPI2_SCK), MMCU14.1
unnamed: M11.N21 (SPI2_MISO), MMCU15.1
unnamed: M11.N22 (SPI2_MOSI), MMCU16.1
unnamed: M11.N23 (SPI2_CS), MMCU17.1
unnamed: M11.N25 (SWCLK), MMCU5.1
unnamed: M11.N26 (SWDIO), MMCU6.1
unnamed: M11.N27 (SWO), MMCU7.1
unnamed: M11.N32 (USBI1D), MMCU8.1
unnamed: M11.S8 (IN_SENS1), MMCU33.1
unnamed: M11.S9 (IN_SENS2), MMCU34.1
unnamed: M11.S10 (IN_SENS3), MMCU35.1
unnamed: M11.S11 (IN_SENS4), MMCU36.1
V5A: M7.E5 (V5A), M7.J1 (PULL_V5A), M7.J5 (PULL_PPS), M7.J7 (PULL_AUX4), M7.J9 (PULL_AUX2), M7.J10 (PULL_AUX1), M7.J17 (PULL_CAM), M7.J18 (PULL_VSS), M7.J19 (PULL_TPS), M7.J20 (PULL_O2S), M7.J21 (PULL_CRANK), M7.N1 (V5A), M8.E1 (V5A), M11.S33 (V5A)
V12_RAW: M1.E2 (V12_RAW), M9.S11 (V12_RAW)

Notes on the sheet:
MOSI
MISO
CLK
1 | Low side | Fuel pump 2 | Low side | ICV close 3 | Low side | Inj 5 4 | Low side | inj 6 5 | Low side | inj 4 6 | GND | gnd injectors 7 | Low side | VVT Solenoid 8 | Low side | CEL 9 | Spare | 10 | Spare | 11 | NC | Trans TPS out 12 | Analogue in | 13 | Analogue in | Lambda signal 14 | GND | MAF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
45 | GND | gnd for shield 46 | Low side | Ti signal (Fuel consumption) 47 | Low side | RPM output 48 | Low side | AC compressor relay pin 85 49 | Spare | 50 | High low | coil 1 51 | High low | coil 2 52 | High low | coil 3 53 | Spare | 54 | 12v+ | 12v from DME relay 55 | GND | gnd ignition 56 | 12v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

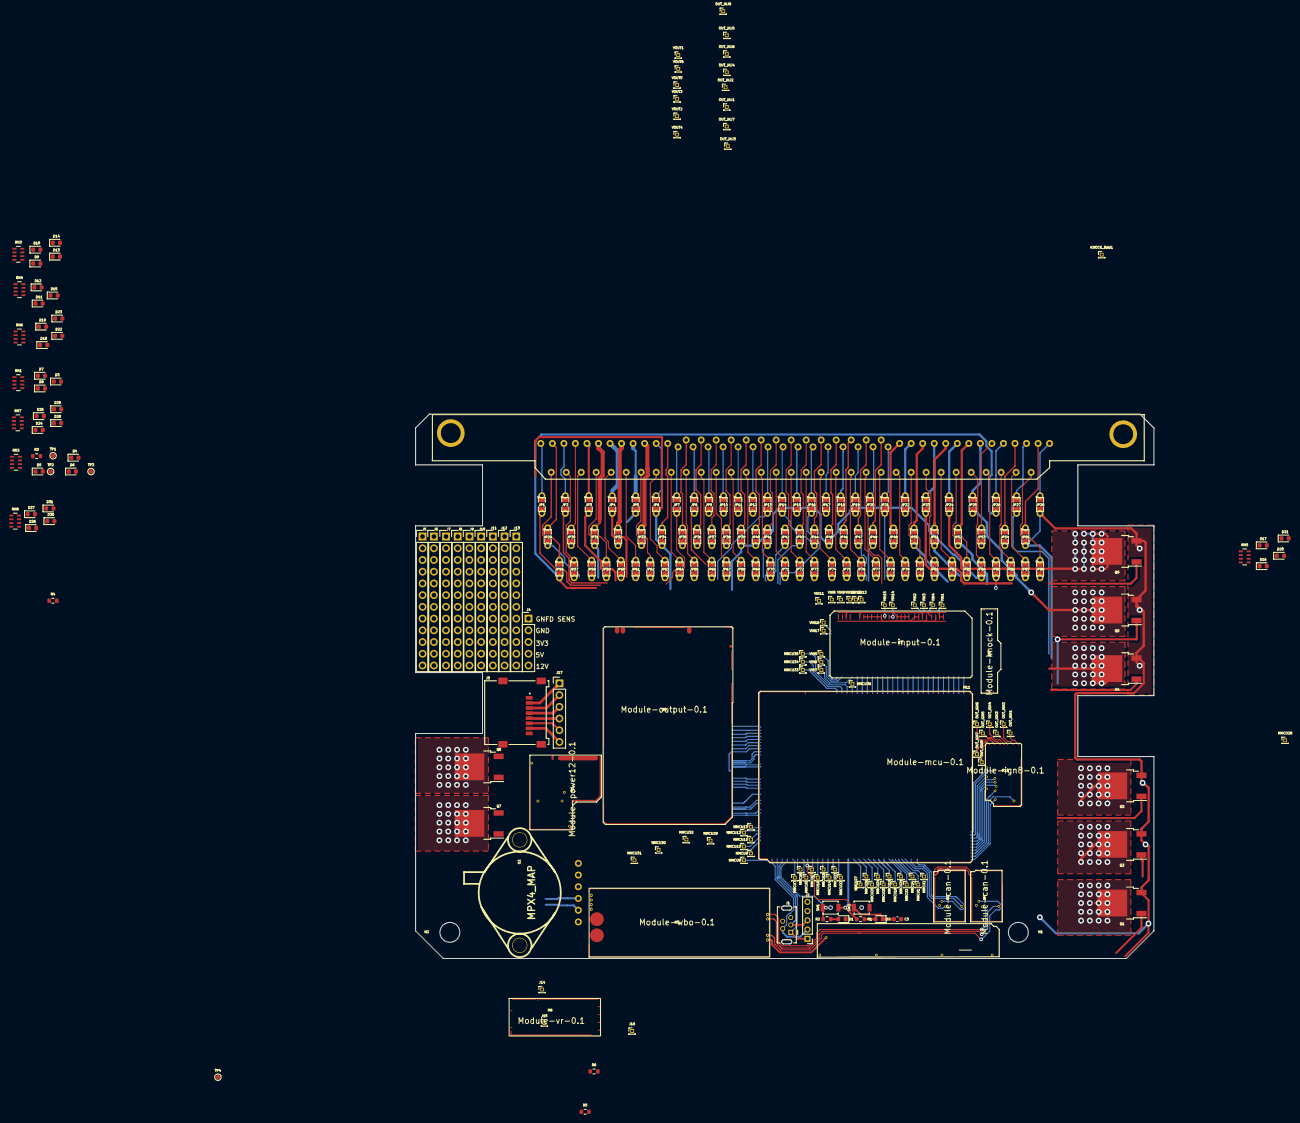
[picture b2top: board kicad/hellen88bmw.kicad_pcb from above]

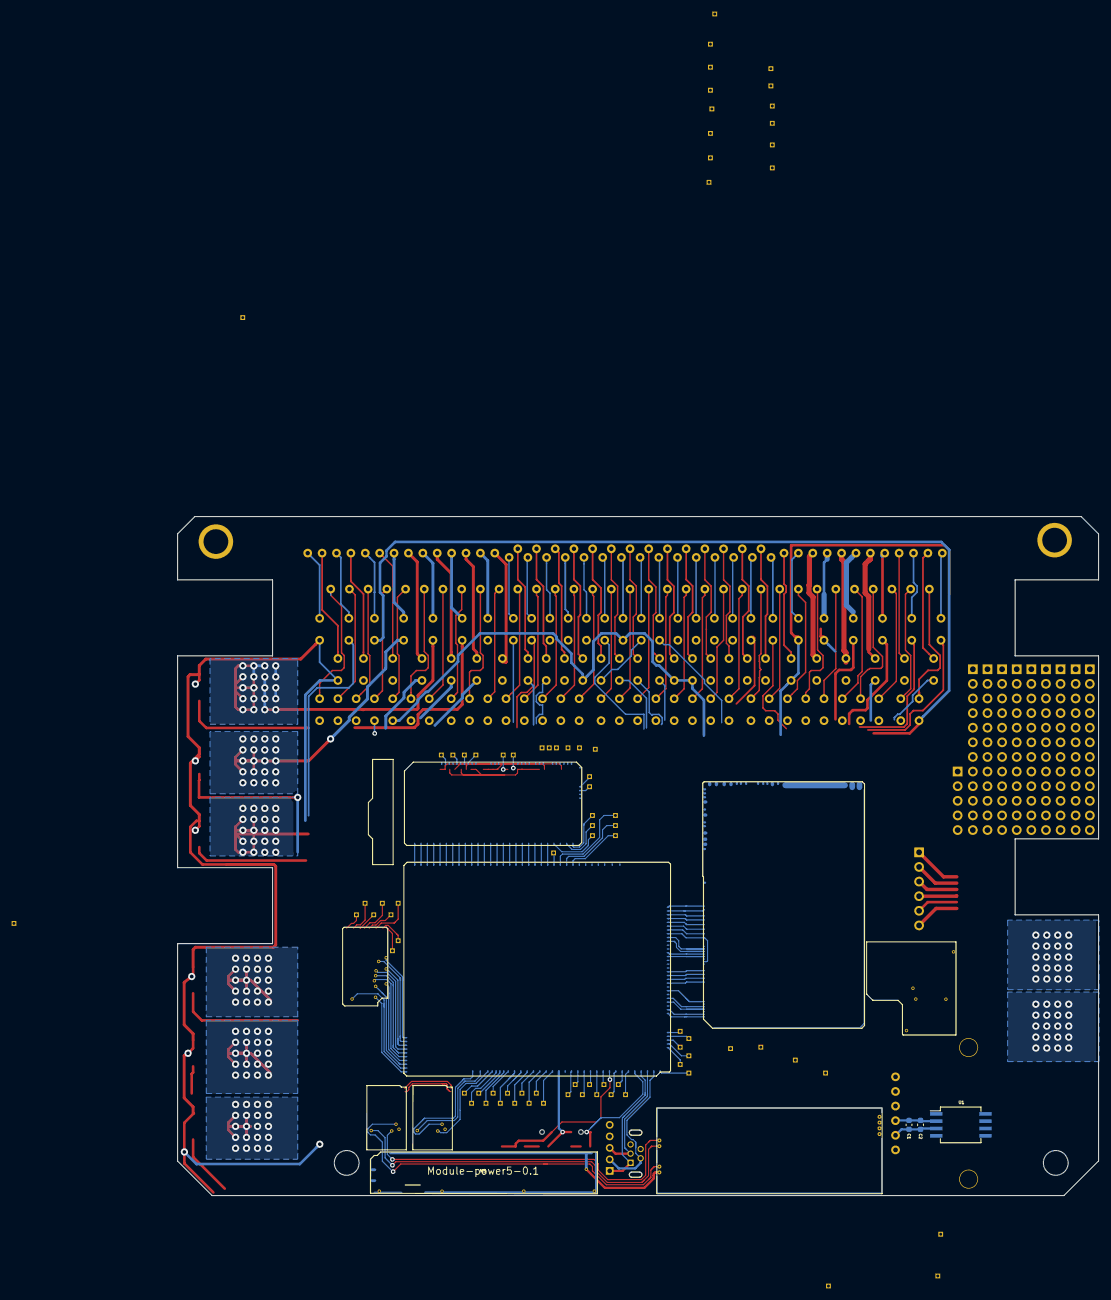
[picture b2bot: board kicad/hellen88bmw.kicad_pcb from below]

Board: 2 copper layers, 160.0 x 118.0 mm, 259 parts (4 on the bottom side), 302 nets.

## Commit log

2021-01-27 frame starting point
2021-03-09 submodule "hellen-one"
2021-03-09 submodules
2021-03-18 Up hellen88
2021-03-18 removing backups
2021-03-21 Up 88bmw update
2021-04-01 Up 88 update
2021-04-26 Up 88
2021-05-20 Please point to local hellen-one submodule #10
2021-06-08 proper location for readme
2021-07-02 Up hellen88bmw
2021-07-05 Up hellen88bmw 5.07.2021
2021-07-06 Up hellen88bmw 6.07.2021
2021-07-14 Up issue 26.28.29
2021-07-14 Up issue 30
2021-07-14 hellen-one scripts
2021-07-21 Up 20/072021
2021-07-22 Up 21/072021
2021-08-03 Up 04/082021
2021-08-12 Up 12/08/2021
2021-08-12 Up 12/08/2021 part 2
2021-08-13 Silkscreen
2021-08-13 14/08/2021
2021-08-14 fix 14/08/2021
2021-08-14 fix 2 14/08/2021
2021-08-15 15/08/2021
2021-08-16 16/08/2021 fix 1
2021-08-16 BOM issues #45
2021-08-16 BOM fix
2021-08-17 BOM fix 17/08/2021
2021-08-17 fix schematic and board
2021-08-23 Issues 61,60,59,57,55,54,17,6,13,8,16,12
2021-08-23 schematic
2021-08-28 update 28/08/2021
2021-08-30 update 29/08/2021
2021-08-31 update 31/08/2021
2021-08-31 lib update 31/08/2021 2
2021-09-03 pcb board
2021-09-04 ETB tracer fix
2021-09-15 Sch refactoring
2021-09-16 PCB refactoring started
2021-09-18 Upd pcb
2021-09-21 DRC fix, test export
2021-09-21 fresh modules
2021-09-21 Export preview
    Problem with SD module on bottom
2021-09-28 Wbo 0.3
2021-10-02 Double side preview
2021-10-02 offset for the composite image
2021-10-02 3d preview
2021-10-02 Fresh export. JLC adjustments
2021-10-04 VIGN fix
2021-10-05 Fresh fab exprot
2021-10-06 DRL fix
2022-06-21 Some fixes
    #34, #46, #43, #45, #23, #33, #28, #3, #27, #49, #48, #47, #44, #26
2022-06-21 Rename replace
2022-06-21 Auto-generated board
2022-06-21 Upd replace
2022-06-23 MCU144
2022-06-23 Fab export
2022-06-25 fresh
2022-06-25 progress
2022-09-21 [skip actions] Auto-generated board
2023-03-16 remove kicad-libraries-private
2023-03-22 Something is funky with PNG #82
    fresh
2023-06-02 update hellen-one submodule
2023-06-02 Use scripts in workflow and install kicad
2023-06-03 install kicad-netlist-reader
2023-07-12 Update to newest hellen-one
2023-07-12 this (public) repo does not need MY_REPO_PAT magic
2023-07-12 we do not want PRs to be pushing generated stuff do we?
2023-07-13 let's support both newer 'main' and older 'master' repositories
2023-07-13 use reusable workflow
2023-07-13 add permissions
2023-07-13 poke
